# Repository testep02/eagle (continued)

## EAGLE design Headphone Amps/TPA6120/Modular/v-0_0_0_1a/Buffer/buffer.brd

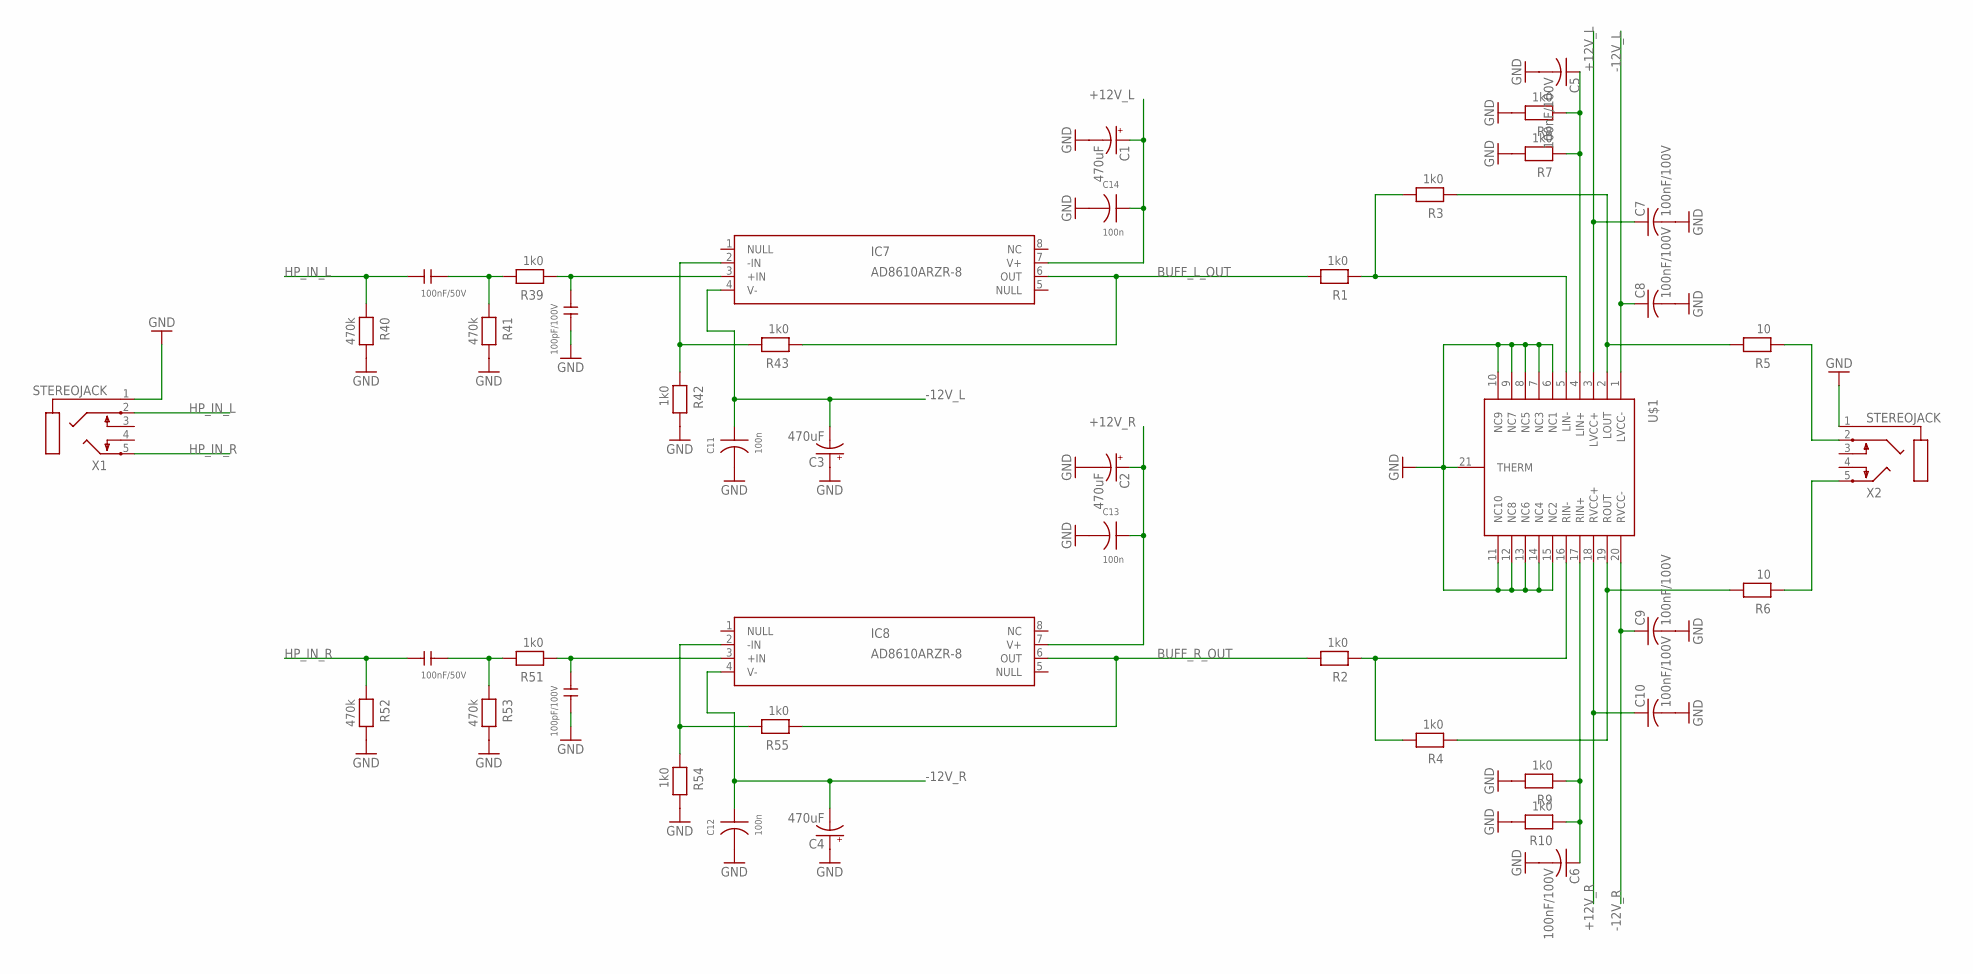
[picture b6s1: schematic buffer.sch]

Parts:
C1, C2, C3, C4: 470uF; E5-13
C5, C6, C7, C8, C9, C10: 100nF/100V; C0402
C11, C12, C13, C14: 100n; R0603
C41, C48: 100nF/50V; 2,5X6,5RM5,0
C42, C49: 100pF/100V; 2,5X7,0RM2,5
IC7, IC8: AD8610ARZR-8; 8-LEAD-SOIC_N
R1, R2, R3, R4, R7, R8, R9, R10, R39, R42, R43, R51, R54, R55: 1k0; R0603
R5, R6: 10; R0805
R40, R41, R52, R53: 470k; R0603
U$1: TPA6120_TPA6120
X1, X2: STEREOJACK; STX3100

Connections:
+12V_L: C1.+, C7.1, C14.P$2, IC7.7 (V+), U$1.3 (LVCC+)
+12V_R: C2.+, C10.1, C13.P$2, IC8.7 (V+), U$1.18 (RVCC+)
-12V_L: C3.-, C8.1, C11.P$2, IC7.4 (V-), U$1.1 (LVCC-)
-12V_R: C4.-, C9.1, C12.P$2, IC8.4 (V-), U$1.20 (RVCC-)
BUFF_L_OUT: IC7.6 (OUT), R1.P$2, R43.P$1
BUFF_R_OUT: IC8.6 (OUT), R2.P$2, R55.P$1
GND: C1.-, C2.-, C3.+, C4.+, C5.2, C6.2, C7.2, C8.2, C9.2, C10.2, C11.P$1, C12.P$1, C13.P$1, C14.P$1, C42.2, C49.2, R7.P$2, R8.P$2, R9.P$2, R10.P$2, R40.P$2, R41.P$2, R42.P$2, R52.P$2, R53.P$2, R54.P$2, U$1.6 (NC1), U$1.7 (NC3), U$1.8 (NC5), U$1.9 (NC7), U$1.10 (NC9), U$1.11 (NC10), U$1.12 (NC8), U$1.13 (NC6), U$1.14 (NC4), U$1.15 (NC2), U$1.21 (THERM), X1.1, X2.1
HP_IN_L: C41.1, R40.P$1, X1.2
HP_IN_R: C48.1, R52.P$1, X1.5
INVERT_L: R1.P$1, R3.P$2, U$1.5 (LIN-)
INVERT_R: R2.P$1, R4.P$2, U$1.16 (RIN-)
unnamed: C5.1, R7.P$1, R8.P$1, U$1.4 (LIN+)
unnamed: C6.1, R9.P$1, R10.P$1, U$1.17 (RIN+)
unnamed: R6.P$1, X2.5
unnamed: R5.P$1, X2.2
unnamed: C41.2, R39.P$2, R41.P$1
unnamed: C42.1, IC7.3 (+IN), R39.P$1
unnamed: IC7.2 (-IN), R42.P$1, R43.P$2
unnamed: C48.2, R51.P$2, R53.P$1
unnamed: C49.1, IC8.3 (+IN), R51.P$1
unnamed: IC8.2 (-IN), R54.P$1, R55.P$2
OUT_L: R3.P$1, R5.P$2, U$1.2 (LOUT)
OUT_R: R4.P$1, R6.P$2, U$1.19 (ROUT)

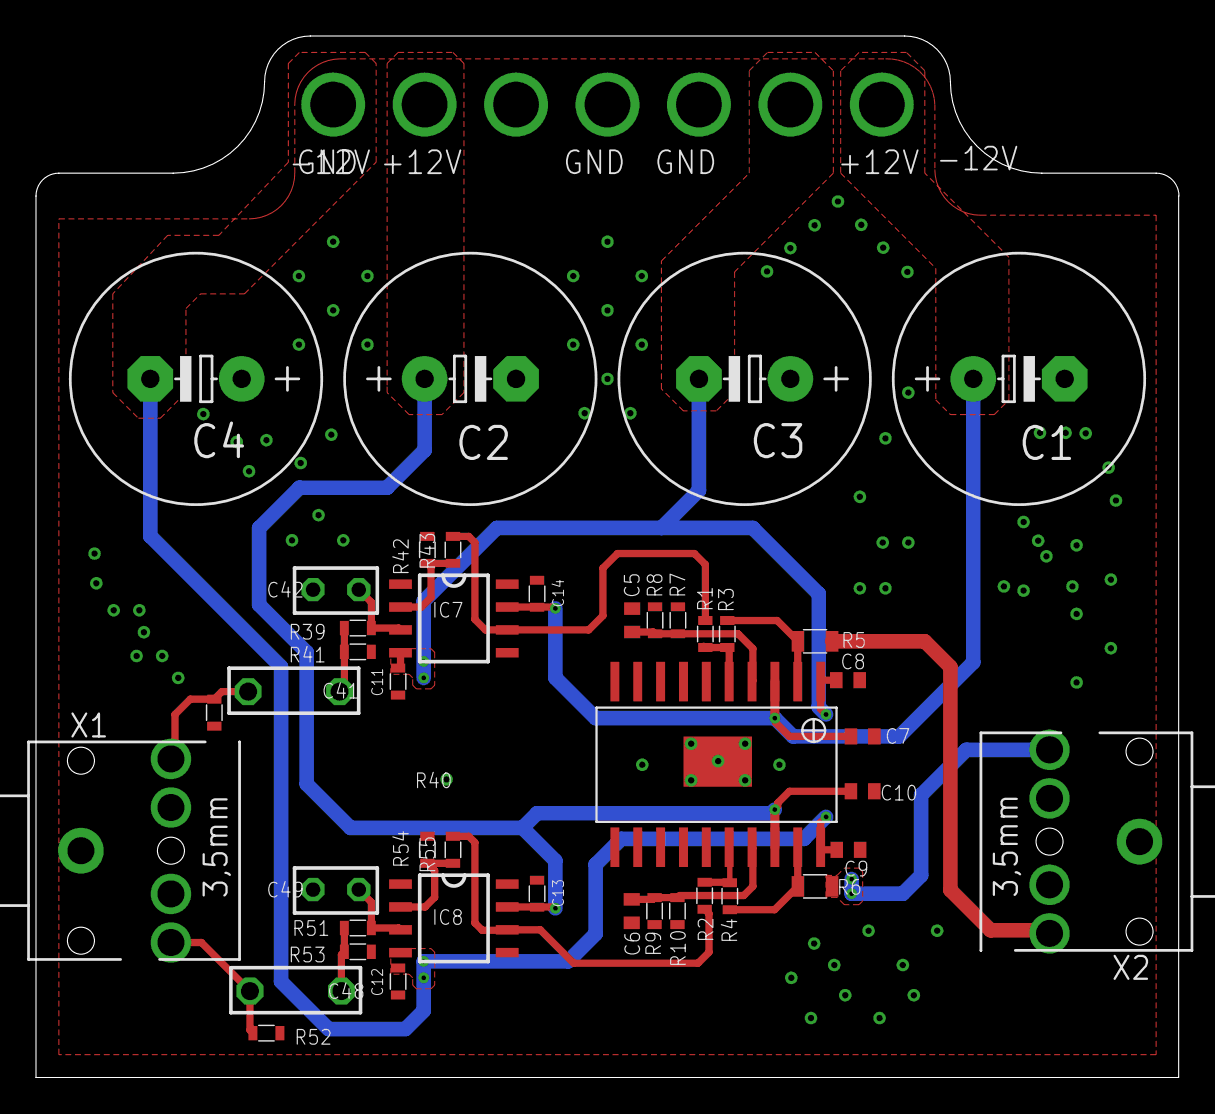
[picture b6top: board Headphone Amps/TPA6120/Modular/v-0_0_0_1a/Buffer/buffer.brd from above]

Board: 2 copper layers, 63.5 x 57.9 mm, 43 parts (0 on the bottom side), 23 nets.
